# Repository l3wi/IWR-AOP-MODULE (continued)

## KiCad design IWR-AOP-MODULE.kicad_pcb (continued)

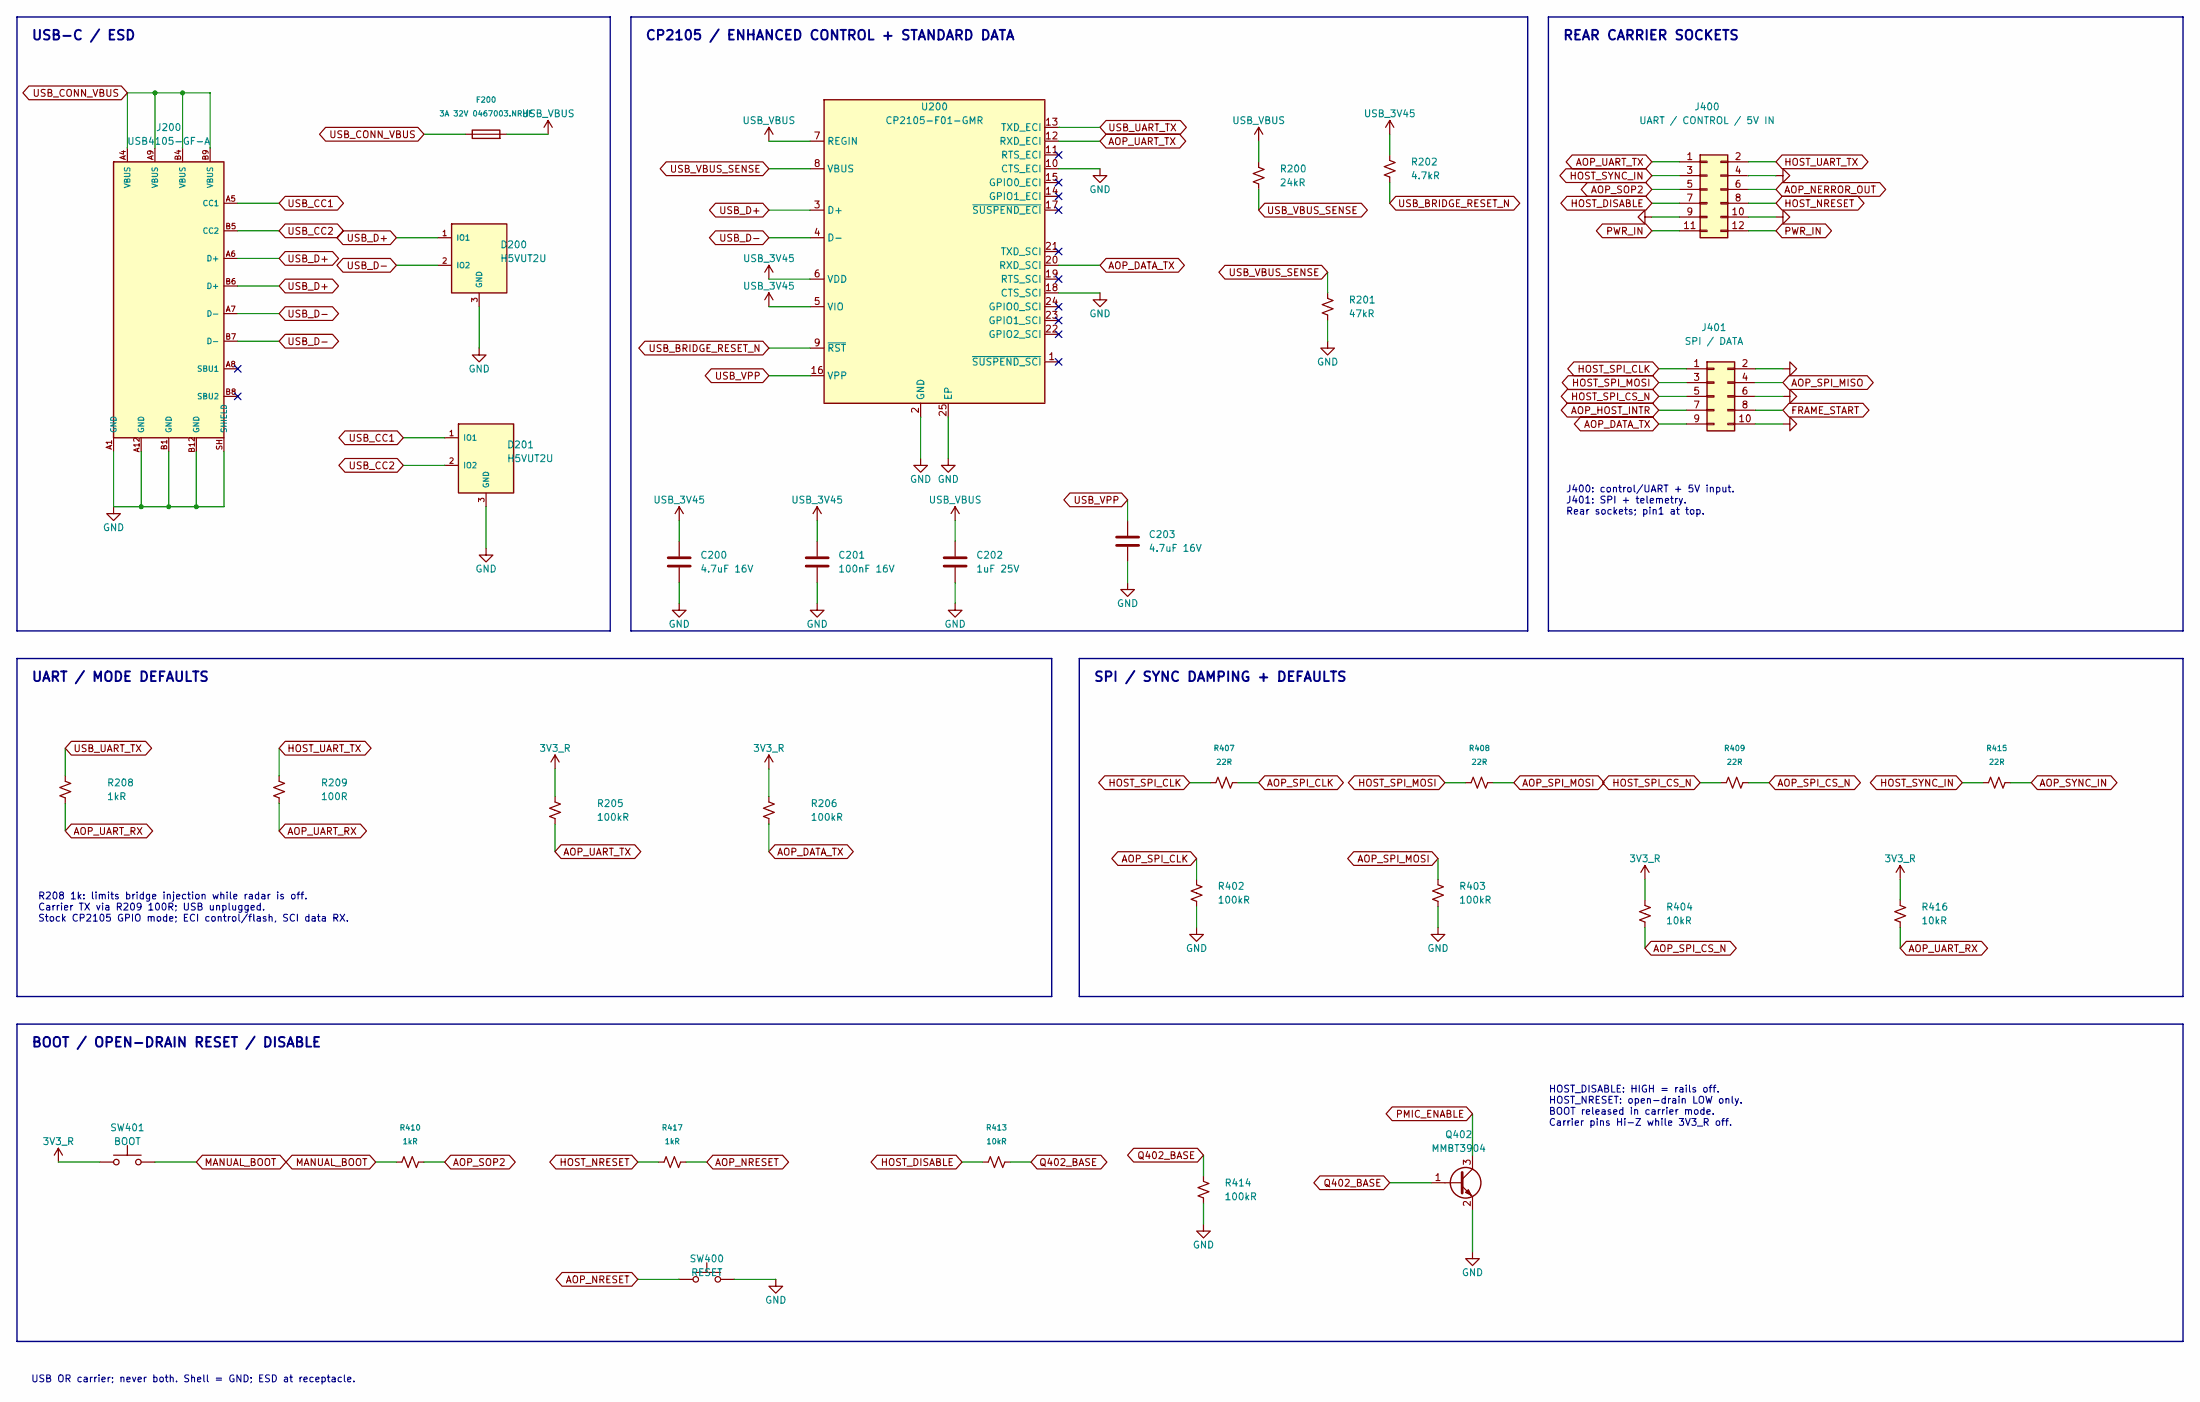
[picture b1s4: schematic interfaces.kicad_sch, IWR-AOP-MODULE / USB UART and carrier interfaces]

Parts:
C200, C203: 4.7uF 16V; C_0805_2012Metric; MPN CL21A475KAQNNNE; LCSC C1779
C201: 100nF 16V; C_0402_1005Metric; MPN CL05B104KO5NNNC; LCSC C1525
C202: 1uF 25V; C_0805_2012Metric; MPN CL21B105KBFNNNE; LCSC C28323
D200, D201: H5VUT2U; SOT-23; MPN H5VUT2U; LCSC C20615824
F200: 3A 32V 0467003.NRHF; Fuse_0603_1608Metric; MPN 0467003.NRHF; LCSC C99558
J200: USB4105-GF-A; USB_C_Receptacle_GCT_USB4105-xx-A_16P_TopMnt_Horizontal; MPN USB4105-GF-A; LCSC C3020560
J400: UART / CONTROL / 5V IN; HCTL_PM254-2-06-S-8.5; MPN PM254-2-06-S-8.5; LCSC C3975151
J401: SPI / DATA; HCTL_PM254-2-05-S-8.5; MPN PM254-2-05-S-8.5; LCSC C3975150
Q402: MMBT3904; SOT-23; MPN MMBT3904; LCSC C20526
R200: 24kR; R_0402_1005Metric; MPN 0402WGF2402TCE; LCSC C25769
R201: 47kR; R_0402_1005Metric; MPN 0402WGF4702TCE; LCSC C25792
R202: 4.7kR; R_0402_1005Metric; MPN 0402WGF4701TCE; LCSC C25900
R205, R206, R402, R403, R414: 100kR; R_0402_1005Metric; MPN 0402WGF1003TCE; LCSC C25741
R208, R410, R417: 1kR; R_0402_1005Metric; MPN 0402WGF1001TCE; LCSC C11702
R209: 100R; R_0402_1005Metric; MPN 0402WGF1000TCE; LCSC C25076
R404, R413, R416: 10kR; R_0402_1005Metric; MPN 0402WGF1002TCE; LCSC C25744
R407, R408, R409, R415: 22R; R_0402_1005Metric; MPN 0402WGF220JTCE; LCSC C25092
SW400: RESET; XKB_TS-1187A-B-A-B_5.1x5.1mm; MPN TS-1187A-B-A-B; LCSC C318884
SW401: BOOT; XKB_TS-1187A-B-A-B_5.1x5.1mm; MPN TS-1187A-B-A-B; LCSC C318884
U200: CP2105-F01-GMR; QFN-24-1EP_4x4mm_P0.5mm_EP2.7x2.6mm; MPN CP2105-F01-GMR; LCSC C109102

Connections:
3V3_R: R205.1, R206.1, R404.1, R416.1, SW401.1; also elsewhere on the board
AOP_DATA_TX: J401.9, R206.2, U200.20 (RXD_SCI); also elsewhere on the board
AOP_HOST_INTR: J401.7; also elsewhere on the board
AOP_NERROR_OUT: J400.6; also elsewhere on the board
AOP_NRESET: R417.2, SW400.1; also elsewhere on the board
AOP_SOP2: J400.5, R410.2; also elsewhere on the board
AOP_SPI_CLK: R402.1, R407.2; also elsewhere on the board
AOP_SPI_CS_N: R404.2, R409.2; also elsewhere on the board
AOP_SPI_MISO: J401.4; also elsewhere on the board
AOP_SPI_MOSI: R403.1, R408.2; also elsewhere on the board
AOP_SYNC_IN: R415.2; also elsewhere on the board
AOP_UART_RX: R208.2, R209.2, R416.2; also elsewhere on the board
AOP_UART_TX: J400.1, R205.2, U200.12 (RXD_ECI); also elsewhere on the board
FRAME_START: J401.8; also elsewhere on the board
GND: C200.2, C201.2, C202.2, C203.2, D200.3 (GND), D201.3 (GND), J200.A1 (GND), J200.A12 (GND), J200.B1 (GND), J200.B12 (GND), J200.SH (SHIELD), J400.4, J400.9, J400.10, J401.2, J401.6, J401.10, Q402.2 (E), R201.2, R402.2, R403.2, R414.2, SW400.2, U200.2 (GND), U200.10 (CTS_ECI), U200.18 (CTS_SCI), U200.25 (EP); also elsewhere on the board
HOST_DISABLE: J400.7, R413.1
HOST_NRESET: J400.8, R417.1
HOST_SPI_CLK: J401.1, R407.1
HOST_SPI_CS_N: J401.5, R409.1
HOST_SPI_MOSI: J401.3, R408.1
HOST_SYNC_IN: J400.3, R415.1
HOST_UART_TX: J400.2, R209.1
MANUAL_BOOT: R410.1, SW401.2
PMIC_ENABLE: Q402.3 (C); also elsewhere on the board
PWR_IN: J400.11, J400.12; also elsewhere on the board
Q402_BASE: Q402.1 (B), R413.2, R414.1
USB_3V45: C200.1, C201.1, R202.1, U200.5 (VIO), U200.6 (VDD)
USB_BRIDGE_RESET_N: R202.2, U200.9 (~RST)
USB_CC1: D201.1 (IO1), J200.A5 (CC1); also elsewhere on the board
USB_CC2: D201.2 (IO2), J200.B5 (CC2); also elsewhere on the board
USB_CONN_VBUS: F200.1, J200.A4 (VBUS), J200.A9 (VBUS), J200.B4 (VBUS), J200.B9 (VBUS)
USB_D+: D200.1 (IO1), J200.A6 (D+), J200.B6 (D+), U200.3 (D+)
USB_D-: D200.2 (IO2), J200.A7 (D-), J200.B7 (D-), U200.4 (D-)
USB_UART_TX: R208.1, U200.13 (TXD_ECI)
USB_VBUS: C202.1, F200.2, R200.1, U200.7 (REGIN); also elsewhere on the board
USB_VBUS_SENSE: R200.2, R201.1, U200.8 (VBUS)
USB_VPP: C203.1, U200.16 (VPP)

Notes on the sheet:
USB-C / ESD
CP2105 / ENHANCED CONTROL + STANDARD DATA
REAR CARRIER SOCKETS
J400: control/UART + 5V input. J401: SPI + telemetry. Rear sockets; pin1 at top.
UART / MODE DEFAULTS
R208 1k: limits bridge injection while radar is off. Carrier TX via R209 100R; USB unplugged. Stock CP2105 GPIO mode; ECI control/flash, SCI data RX.
SPI / SYNC DAMPING + DEFAULTS
BOOT / OPEN-DRAIN RESET / DISABLE
HOST_DISABLE: HIGH = rails off. HOST_NRESET: open-drain LOW only. BOOT released in carrier mode. Carrier pins Hi-Z while 3V3_R off.
USB OR carrier; never both. Shell = GND; ESD at receptacle.

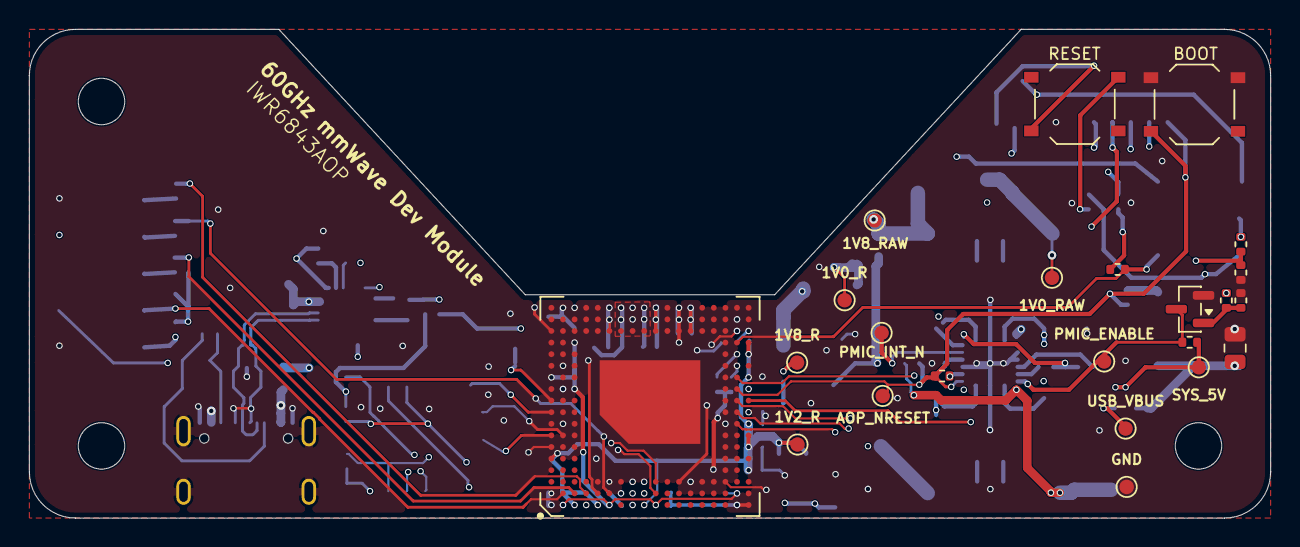
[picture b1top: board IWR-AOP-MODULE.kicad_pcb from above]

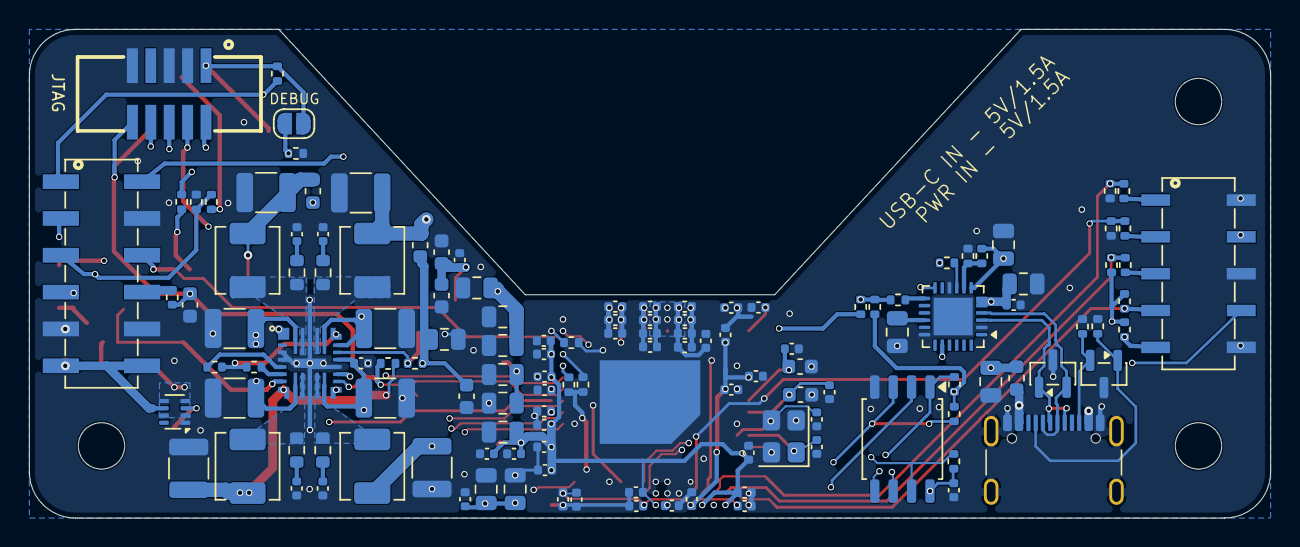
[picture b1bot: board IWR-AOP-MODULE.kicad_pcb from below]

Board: 6 copper layers, 85.6 x 33.7 mm, 158 parts (131 on the bottom side), 74 nets.

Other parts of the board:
H1, H3, H4: MountingHole_3.2mm_M3
TH300: AOP_ALP180_DieThermalPad

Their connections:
GND: TH300.1; also elsewhere on the board

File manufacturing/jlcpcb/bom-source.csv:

"Comment","Designator","Footprint","LCSC","Qty","MPN","Manufacturer","Tolerance","Rating"
"0R","R314,R604","Resistor_SMD:R_0402_1005Metric","C17168","2","0402WGF0000TCE","UNI-ROYAL(Uniroyal Elec)","",""
"18pF","C346,C347","Capacitor_SMD:C_0402_1005Metric","C1549","2","0402CG180J500NT","FH (Guangdong Fenghua Advanced Tech)","",""
"390pF","C614,C615,C616,C617","Capacitor_SMD:C_0402_1005Metric","C76967","4","GRM1555C1H391JA01D","Murata Electronics","5%","C0G 50V"
"47nF","C345","Capacitor_SMD:C_0402_1005Metric","C77017","1","GRM155R71E473KA88D","Murata","",""
"100nF","C301,C302,C303,C304,C305,C306,C307,C308,C309,C310,C311,C314,C315,C316,C317,C318,C319,C322,C323,C324,C325,C326,C327,C328,C329,C330,C331,C332,C333,C335,C336,C338,C340,C342,C343,C344,C348,C604,C622,C623,C706","Capacitor_SMD:C_0402_1005Metric","C1525","41","CL05B104KO5NNNC","Samsung Electro-Mechanics","",""
"0.47uH","L600,L601,L602,L603","Inductor_SMD:L_Sunlord_MWSA0402S","C6331050","4","MWSA0402S-R47MT","Sunlord","",""
"1uF","C313,C321,C337,C339","Capacitor_SMD:C_0603_1608Metric","C15849","4","CL10A105KB8NNNC","Samsung Electro-Mechanics","",""
"4.7uF","C341","Capacitor_SMD:C_0603_1608Metric","C19666","1","CL10A475KO8NNNC","Samsung Electro-Mechanics","",""
"10uF","C300,C312,C320,C334","Capacitor_SMD:C_0805_2012Metric","C15850","4","CL21A106KAYNNNE","Samsung Electro-Mechanics","",""
"10uF","C620,C621,C629","Capacitor_SMD:C_0805_2012Metric","C86038","3","GRM21BR71A106KE51L","Murata Electronics","10%","X7R 10V"
"22uF","C600,C601,C602,C603,C610,C611,C612,C613","Capacitor_SMD:C_1210_3225Metric","C21397","8","GRM32ER71E226KE15L","Murata Electronics","10%","X7R 25V"
"22uF","C624,C625","Capacitor_SMD:C_0805_2012Metric","C45783","2","CL21A226MAQNNNE","Samsung Electro-Mechanics","20%","X5R 25V"
"1kR","R208,R410,R417","Resistor_SMD:R_0402_1005Metric","C11702","3","0402WGF1001TCE","UNI-ROYAL(Uniroyal Elec)","",""
"3.9R","R610,R611,R612,R613","Resistor_SMD:R_0603_1608Metric","C482845","4","RC0603FR-073R9L","YAGEO","1%","100mW"
"4.7kR","R202","Resistor_SMD:R_0402_1005Metric","C25900","1","0402WGF4701TCE","UNI-ROYAL(Uniroyal Elec)","",""
"10kR","R133,R300,R304,R305,R306,R307,R308,R309,R310,R311,R312,R313,R404,R413,R416,R600,R601,R602,R603","Resistor_SMD:R_0402_1005Metric","C25744","19","0402WGF1002TCE","UNI-ROYAL(Uniroyal Elec)","",""
"22R","R407,R408,R409,R415","Resistor_SMD:R_0402_1005Metric","C25092","4","0402WGF220JTCE","UNI-ROYAL(Uniroyal Elec)","",""
"24kR","R200","Resistor_SMD:R_0402_1005Metric","C25769","1","0402WGF2402TCE","UNI-ROYAL(Uniroyal Elec)","",""
"47kR","R201","Resistor_SMD:R_0402_1005Metric","C25792","1","0402WGF4702TCE","UNI-ROYAL(Uniroyal Elec)","",""
"100R","R209","Resistor_SMD:R_0402_1005Metric","C25076","1","0402WGF1000TCE","UNI-ROYAL(Uniroyal Elec)","",""
"100kR","R205,R206,R402,R403,R414","Resistor_SMD:R_0402_1005Metric","C25741","5","0402WGF1003TCE","UNI-ROYAL(Uniroyal Elec)","",""
"40MHz","Y300","Crystal:Crystal_SMD_3225-4Pin_3.2x2.5mm","C18214314","1","XL2EL89COI-111YLC-40M","YXC Crystal Oscillators","",""
"100nF 16V","C201","Capacitor_SMD:C_0402_1005Metric","C1525","1","CL05B104KO5NNNC","Samsung Electro-Mechanics","",""
"10uF 10V","C140","Capacitor_SMD:C_0805_2012Metric","C86038","1","GRM21BR71A106KE51L","Murata Electronics","",""
"120R@100MHz / 3A","FB600,FB601","Inductor_SMD:L_0603_1608Metric","C437404","2","BLM18KG121TH1D","Murata","",""
"1uF 25V","C100,C202","Capacitor_SMD:C_0805_2012Metric","C28323","2","CL21B105KBFNNNE","Samsung Electro-Mechanics","",""
"3A 32V 0467003.NRHF","F200","Fuse:Fuse_0603_1608Metric","C99558","1","0467003.NRHF","Littelfuse","",""
"4.7uF 16V","C200,C203","Capacitor_SMD:C_0805_2012Metric","C1779","2","CL21A475KAQNNNE","Samsung Electro-Mechanics","",""
"5.1kR 1%","R100,R101","Resistor_SMD:R_0402_1005Metric","C25905","2","0402WGF5101TCE","UNI-ROYAL(Uniroyal Elec)","",""
"BOOT","SW401","IWR-AOP-MODULE:XKB_TS-1187A-B-A-B_5.1x5.1mm","C318884","1","TS-1187A-B-A-B","XKB Connection","",""
"CP2105-F01-GMR","U200","Package_DFN_QFN:QFN-24-1EP_4x4mm_P0.5mm_EP2.7x2.6mm","C109102","1","CP2105-F01-GMR","Silicon Laboratories","",""
"H5VUT2U","D200,D201","Package_TO_SOT_SMD:SOT-23","C20615824","2","H5VUT2U","hongjiacheng","",""
"IWR6843ARQGALPR","U300","IWR-AOP-MODULE:BGA180C80P18X18_1500X1500X97N","C2871887","1","IWR6843ARQGALPR","Texas Instruments","",""
"LM66200DRLR","U117","Package_TO_SOT_SMD:SOT-583-8","C3235556","1","LM66200DRLR","Texas Instruments","",""
"LP87524JRNFRQ1","U600","IWR-AOP-MODULE:Texas_RNF0026C_LP87524J","C701982","1","LP87524JRNFRQ1","Texas Instruments","",""
"MMBT3904","Q402","Package_TO_SOT_SMD:SOT-23","C20526","1","MMBT3904","Jiangsu Changjing Electronics Technology Co., Ltd.","",""
"MX25L3233FM2I-08G","U301","Package_SO:SOIC-8_5.3x5.3mm_P1.27mm","C190802","1","MX25L3233FM2I-08G","Macronix","",""
"RADAR JTAG","J301","IWR-AOP-MODULE:XKB_X1270WVS-2x05B-9TV01_2x05_P1.27mm_Vertical","C2962219","1","X1270WVS-2x05B-9TV01","XKB Connection","",""
"RESET","SW400","IWR-AOP-MODULE:XKB_TS-1187A-B-A-B_5.1x5.1mm","C318884","1","TS-1187A-B-A-B","XKB Connection","",""
"SPI / DATA","J401","IWR-AOP-MODULE:HCTL_PM254-2-05-S-8.5","C3975150","1","PM254-2-05-S-8.5","HCTL","",""
"UART / CONTROL / 5V IN","J400","IWR-AOP-MODULE:HCTL_PM254-2-06-S-8.5","C3975151","1","PM254-2-06-S-8.5","HCTL","",""
"USB4105-GF-A","J200","Connector_USB:USB_C_Receptacle_GCT_USB4105-xx-A_16P_TopMnt_Horizontal","C3020560","1","USB4105-GF-A","Global Connector Technology","",""
